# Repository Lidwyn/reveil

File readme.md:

# Alarm Clock Project

A fully custom-built **embedded alarm clock** designed from scratch, featuring a hardware-level implementation using an **ATmega328P**, **7-segment displays**, a **real-time clock (RTC)** module, and a modular audio system with microSD song storage.
This project integrates **embedded firmware**, **electronics design**, **PCB layout**, **CAD**, and **technical documentation**.

> This project is **still in progress**, every features or documents mentionned here might **not be complete or avaible yet**.

## Features
+ **Times display**
+ **Next alarm** on secondary display
+ Up to **15 one time (unique) and 15 weekly (non unique) independent alarms**
+ **Night Mode** - complete display blackout
+ **RTC-based accurate timekeeping** (with battery backup)

## Tech Stack & Tools

### Firmware
+ **Atmega328P** (bare-metal Arduino-style development)
+ **Arduino language** via **PlatformIO**
+ Interrupt-drivern logic
+ Low-power modes

### Elecrtonics & PCB
+ **Kicad** for schematic capture and PCB layout
+ Multi-voltage power stage (5V and 3.3V)

### Mechanical Design
+ **CATIA** for enclosure & mechanical parts

### Documentation
+ **LaTeX** for the user and technical manuals

## Project Architure
```
/Prog/          -> PlatformIO project for MCU firmware
/Schematic/     -> KiCad schematics & PCB files
/cad/           -> CATIA models for enclosure
/Latex/         -> Latex (and pdf) manual
```

## How It Works
1. The **ATmega328P** handles alarm logic, display control, and power management.
2. A **DS3231 RTC** maintains accurate time with battery backup. Through **I2C bus**.
3. On the same chips as the DS3231, we have an **AT24C32 EEPROM** that store the multiples alarms, the volume, and the brightness setup. Also with battery backup and through the same **I2C bus**.
4. Two four **7-segment display** and **9 leds**, driven by two **MAX7219** are in charge of the display. Through **SPI bus**.
5. A **DFPlayer** handle the audio, stored on a **microSD card**, with an integrated amplifier and an external speaker. Through a **Serial Port bus**.
5. 6 buttons for setup.

Find more information about the GUI on the manual:
- [Manuel fr](Latex/Manuel.pdf)

## Learning Objectives & Personal Development
This project in an opportunity to build **foundational embedded-systems skills** from scratch, inculding:
+ **Embedded C++ developpement** on microcontrollers
+ Designing and debugging **digital and mixed-signal electronics**
+ Understanting **RTCs**, **SD interfaces**, **multiplexing**, and **interrupt-driven systems**
+ **PCB worklow** from schematic to layout to fabrication
+ **Mechanical design** for electronics
+ Writing **clear and precise technical documentation** in **LaTeX**

## What I'm Most Proud Of
+ Implementing **deep sleep and interrupt-driven wake-up**, dramatically
reducing power consumption
+ Designing a **clean dual-voltage system** that support both 5V and 3.3V as the ATmega328P consumme less current at 3.3V further improving power consumption
+ Using **logical Mosfet** to cut unactive chips such as the audio chips, reducing noise to zero and reducing consumption
+ **Creating the entire device end-to-end** : firmware, electonics, PCB, mechanical parts, and documentation
+ Gaining practical **embedded engineering experience** from low to no prior knowledge

## How to Build / Run
### Hardware
1. Burn bootloader on the ATmega328P
2. Flash your microSD on FAT32
3. Insert microSD with you preferred alarm audio file with this typo `0001WhateverName.mp3`

### Firmware
1. Install **PlatformIO** (VS Codium extension)
2. Plug the alarm clock
3. Plug your computer into the USB C to seral adapter of the card
4. Adjust `upload_port = COM15` to your specific usb port in `/Prog/platformio.ini`
5. Upload firmware with `pio run --target upload`

## Status
This project is **still in development** :
+ Firmware : **working**, new features should be added and bugs fixed
+ PCB : **schematic is done**, PCB layout is not
+ Mechanical part : not started
+ Documenation : just the base of the french user manual version

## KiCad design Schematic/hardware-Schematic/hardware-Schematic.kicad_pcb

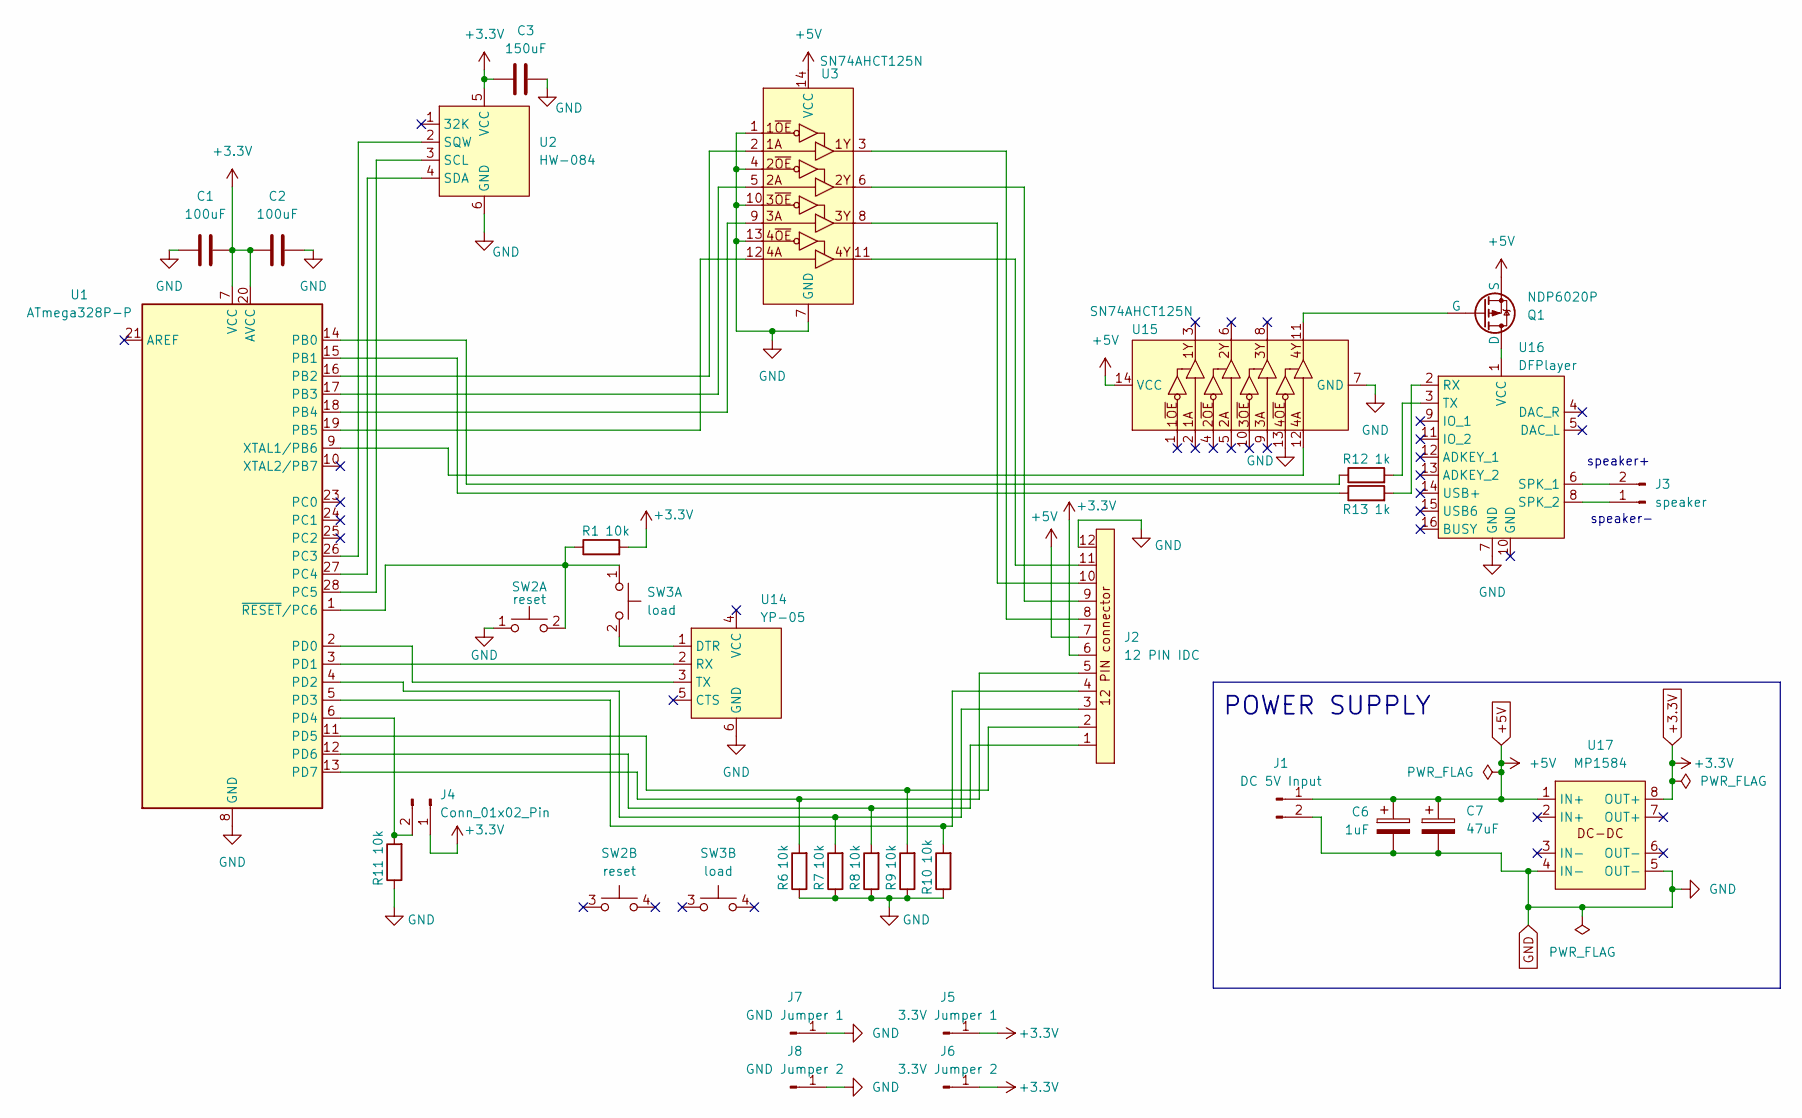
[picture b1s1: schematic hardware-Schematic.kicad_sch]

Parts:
C1, C2: 100uF; C_Axial_L12.0mm_D6.5mm_P15.00mm_Horizontal
C3: 150uF; C_Rect_L7.2mm_W3.0mm_P5.00mm_FKS2_FKP2_MKS2_MKP2
C6: 1uF; CP_Radial_D5.0mm_P2.50mm
C7: 47uF; CP_Radial_D5.0mm_P2.50mm
J1: DC 5V Input; USB-C DC input 5V
J2: 12 PIN IDC; IDC-Header_2x06_P2.54mm_Vertical
J3: speaker; TopButton
J4: Conn_01x02_Pin; R_Axial_DIN0207_L6.3mm_D2.5mm_P10.16mm_Horizontal
J5: 3.3V Jumper 1; Pin_D0.7mm_L6.5mm_W1.8mm_FlatFork
J6: 3.3V Jumper 2; Pin_D0.7mm_L6.5mm_W1.8mm_FlatFork
J7: GND Jumper 1; Pin_D0.7mm_L6.5mm_W1.8mm_FlatFork
J8: GND Jumper 2; Pin_D0.7mm_L6.5mm_W1.8mm_FlatFork
Q1: NDP6020P; TO-220F-3_Vertical
R1, R6, R7, R8, R9, R10, R11: 10k; R_Axial_DIN0207_L6.3mm_D2.5mm_P10.16mm_Horizontal
R12, R13: 1k; R_Axial_DIN0207_L6.3mm_D2.5mm_P10.16mm_Horizontal
SW2: reset; SW_PUSH_6mm
SW3: load; SW_PUSH_6mm
U1: ATmega328P-P; DIP-28_W7.62mm
U2: HW-084; HW-084_YP-05
U3, U15: SN74AHCT125N; DIP-14_W7.62mm
U14: YP-05; HW-084_YP-05
U16: DFPlayer
U17: MP1584

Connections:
+3.3V: C1.2, C2.1, C3.1, J2.6, J4.1, J5.1, J6.1, R1.2, U1.7 (VCC), U1.20 (AVCC), U2.5 (VCC), U17.8 (OUT+)
+5V: C6.1, C7.1, J1.1, J2.7, Q1.3 (S), U3.14 (VCC), U15.14 (VCC), U17.1 (IN+)
GND: C1.1, C2.2, C3.2, C6.2, C7.2, J1.2, J2.12, J7.1, J8.1, R6.1, R7.1, R8.1, R9.1, R10.1, R11.1, SW2.1 (C), U1.8 (GND), U1.22 (GND), U2.6 (GND), U3.1, U3.4, U3.7 (GND), U3.10, U3.13, U14.6 (GND), U15.7 (GND), U15.13, U16.7 (GND), U17.4 (IN-), U17.5 (OUT-)
unnamed: J2.8, U3.3
unnamed: J2.9, U3.6
unnamed: J2.10, U3.8
unnamed: J2.11, U3.11
unnamed: J3.1, U16.8 (SPK_2)
unnamed: J3.2, U16.6 (SPK_1)
unnamed: J4.2, R11.2, U1.6 (PD4)
unnamed: Q1.1 (D), U16.1 (VCC)
unnamed: Q1.2 (G), U15.11
unnamed: R1.1, SW2.2 (D), SW3.1 (C), U1.1 (~RESET/PC6)
unnamed: SW3.2 (D), U14.1 (DTR)
unnamed: R12.1, U1.14 (PB0)
unnamed: R13.1, U1.15 (PB1)
unnamed: U1.16 (PB2), U3.2
unnamed: U1.17 (PB3), U3.5
unnamed: U1.18 (PB4), U3.9
unnamed: U1.19 (PB5), U3.12
unnamed: U1.26 (PC3), U2.2 (SQW)
unnamed: U1.27 (PC4), U2.4 (SDA)
unnamed: U1.28 (PC5), U2.3 (SCL)
unnamed: U1.2 (PD0), U14.3 (TX)
unnamed: U1.3 (PD1), U14.2 (RX)
unnamed: J2.3, R7.2, U1.4 (PD2)
unnamed: J2.4, R10.2, U1.5 (PD3)
unnamed: J2.2, R9.2, U1.11 (PD5)
unnamed: J2.1, R8.2, U1.12 (PD6)
unnamed: J2.5, R6.2, U1.13 (PD7)
unnamed: U1.9 (XTAL1/PB6), U15.12
unnamed: R13.2, U16.2 (RX)
unnamed: R12.2, U16.3 (TX)

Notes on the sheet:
POWER SUPPLY
speaker+
speaker-

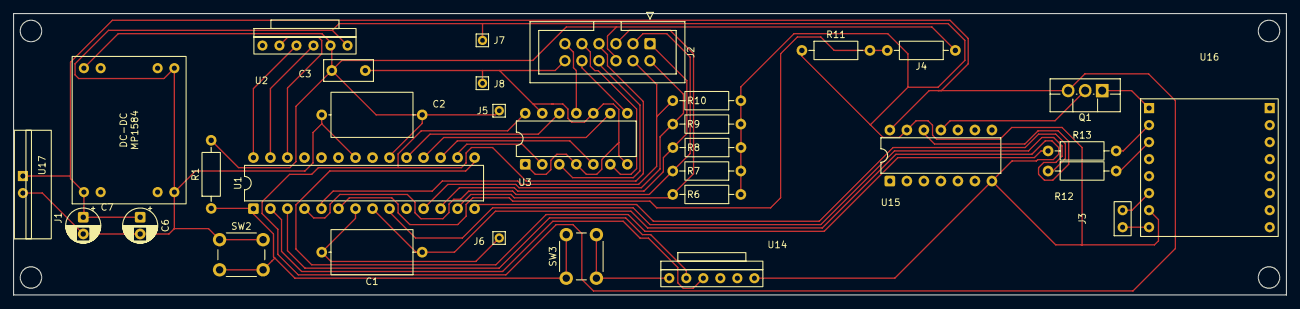
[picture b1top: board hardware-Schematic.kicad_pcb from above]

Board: 2 copper layers, 190.0 x 42.0 mm, 32 parts (0 on the bottom side), 33 nets.

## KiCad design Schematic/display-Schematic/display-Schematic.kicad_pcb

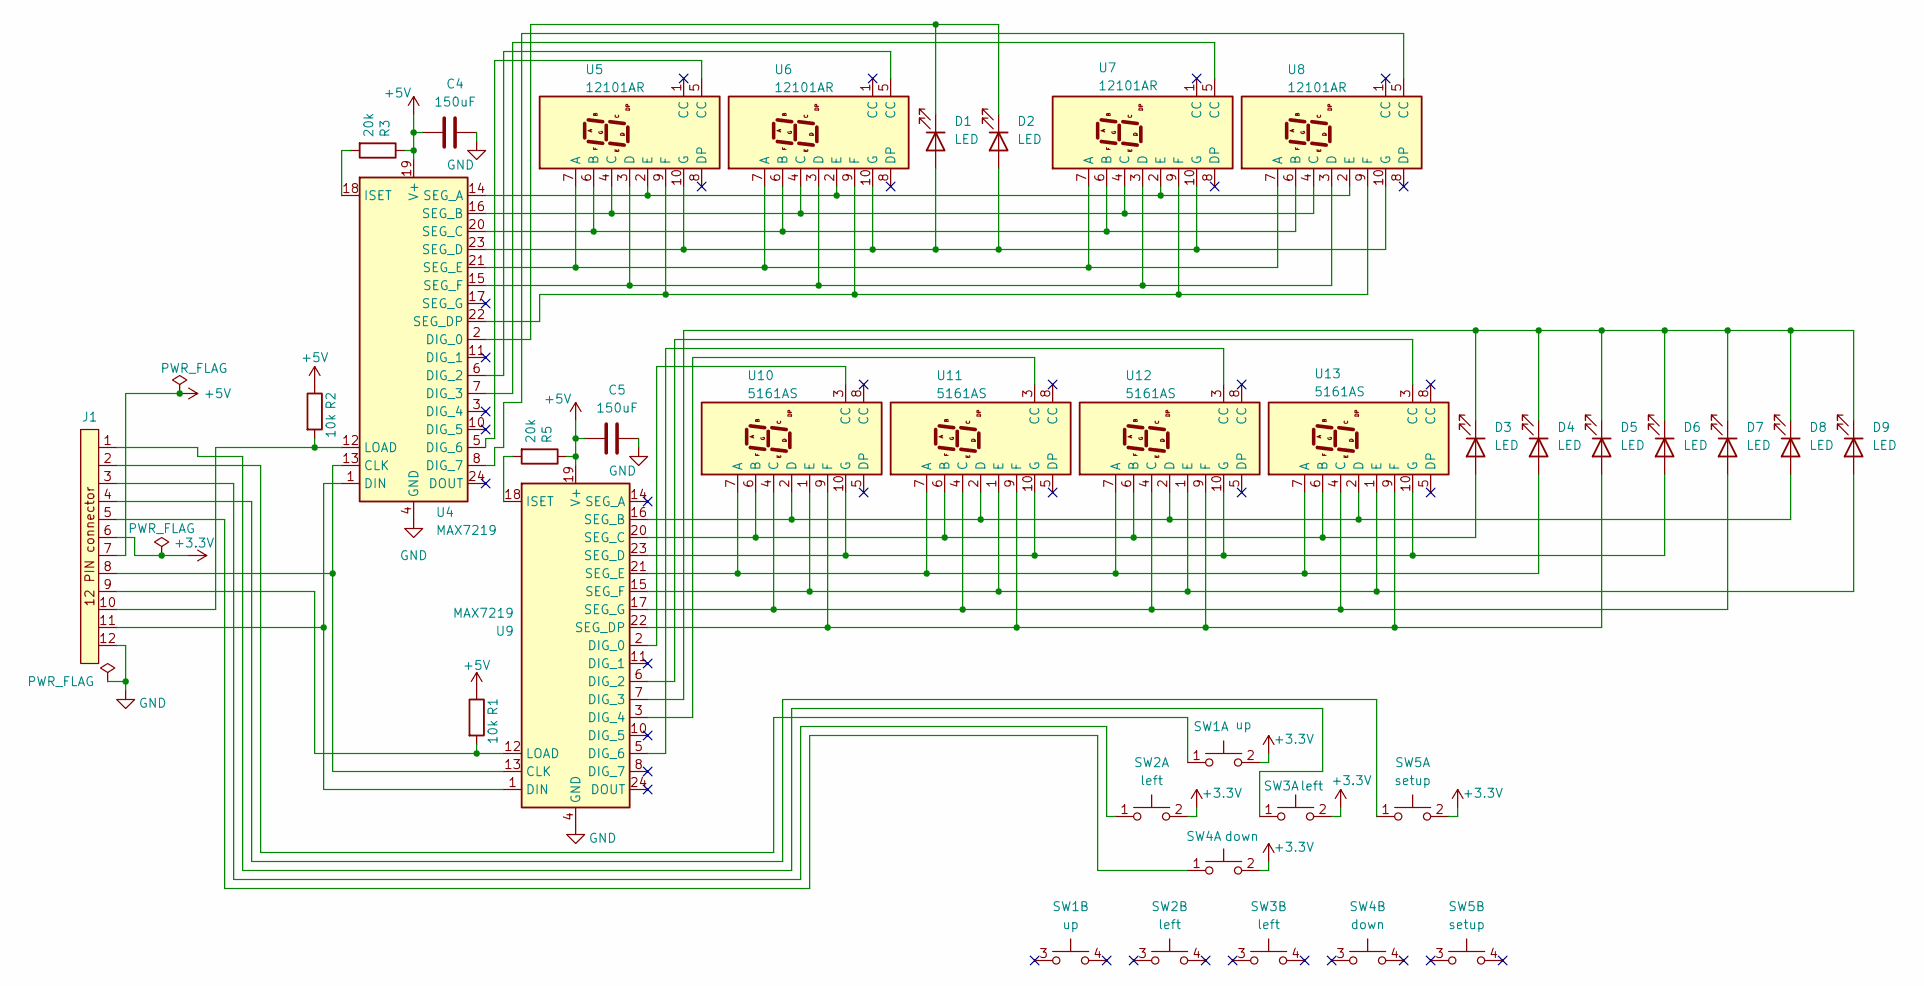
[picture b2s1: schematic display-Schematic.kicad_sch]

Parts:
C4, C5: 150uF; C_Rect_L7.2mm_W3.0mm_P5.00mm_FKS2_FKP2_MKS2_MKP2
D1, D2, D3, D4, D5, D6, D7, D8, D9: LED; LED_D5.0mm
J1: IDC-Header_2x06_P2.54mm_Vertical
R1, R2: 10k; R_Axial_DIN0207_L6.3mm_D2.5mm_P10.16mm_Horizontal
R3, R5: 20k; R_Axial_DIN0207_L6.3mm_D2.5mm_P10.16mm_Horizontal
SW1: up; SW_PUSH_6mm
SW2, SW3: left; SW_PUSH_6mm
SW4: down; SW_PUSH_6mm
SW5: setup; SW_PUSH_6mm
U4, U9: MAX7219; DIP-24_W7.62mm
U5, U6, U7, U8: 12101AR
U10, U11, U12, U13: 5161AS

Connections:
+3.3V: J1.6, SW1.2 (D), SW2.2 (D), SW3.2 (D), SW4.2 (D), SW5.2 (D)
+5V: C4.1, C5.1, J1.7, R1.1, R2.1, R3.1, R5.1, U4.19 (V+), U9.19 (V+)
GND: C4.2, C5.2, J1.12, U4.4 (GND), U4.9 (GND), U9.4 (GND), U9.9 (GND)
unnamed: D1.2 (A), D2.2 (A), U4.23 (SEG_D), U5.10 (G), U6.10 (G), U7.10 (G), U8.10 (G)
unnamed: D1.1 (K), D2.1 (K), U4.2 (DIG_0)
unnamed: D3.2 (A), U9.20 (SEG_C), U10.6 (B), U11.6 (B), U12.6 (B), U13.6 (B)
unnamed: D3.1 (K), D4.1 (K), D5.1 (K), D6.1 (K), D7.1 (K), D8.1 (K), D9.1 (K), U9.7 (DIG_3)
unnamed: D4.2 (A), U9.21 (SEG_E), U10.7 (A), U11.7 (A), U12.7 (A), U13.7 (A)
unnamed: D5.2 (A), U9.22 (SEG_DP), U10.9 (F), U11.9 (F), U12.9 (F), U13.9 (F)
unnamed: D6.2 (A), U9.23 (SEG_D), U10.10 (G), U11.10 (G), U12.10 (G), U13.10 (G)
unnamed: D7.2 (A), U9.17 (SEG_G), U10.4 (C), U11.4 (C), U12.4 (C), U13.4 (C)
unnamed: D8.2 (A), U9.16 (SEG_B), U10.2 (D), U11.2 (D), U12.2 (D), U13.2 (D)
unnamed: D9.2 (A), U9.15 (SEG_F), U10.1 (E), U11.1 (E), U12.1 (E), U13.1 (E)
unnamed: J1.2, SW1.1 (C)
unnamed: J1.3, SW2.1 (C)
unnamed: J1.1, SW3.1 (C)
unnamed: J1.5, SW4.1 (C)
unnamed: J1.4, SW5.1 (C)
unnamed: J1.8, U4.13 (CLK), U9.13 (CLK)
unnamed: U4.6 (DIG_2), U6.5 (CC)
unnamed: U4.7 (DIG_3), U7.5 (CC)
unnamed: U4.5 (DIG_6), U5.5 (CC)
unnamed: U4.8 (DIG_7), U8.5 (CC)
unnamed: J1.11, U4.1 (DIN), U9.1 (DIN)
unnamed: R3.2, U4.18 (ISET)
unnamed: J1.10, R2.2, U4.12 (LOAD)
unnamed: U4.14 (SEG_A), U5.2 (E), U6.2 (E), U7.2 (E), U8.2 (E)
unnamed: U4.16 (SEG_B), U5.4 (C), U6.4 (C), U7.4 (C), U8.4 (C)
unnamed: U4.20 (SEG_C), U5.6 (B), U6.6 (B), U7.6 (B), U8.6 (B)
unnamed: U4.22 (SEG_DP), U5.9 (F), U6.9 (F), U7.9 (F), U8.9 (F)
unnamed: U4.21 (SEG_E), U5.7 (A), U6.7 (A), U7.7 (A), U8.7 (A)
unnamed: U4.15 (SEG_F), U5.3 (D), U6.3 (D), U7.3 (D), U8.3 (D)
unnamed: U9.2 (DIG_0), U10.3 (CC)
unnamed: U9.6 (DIG_2), U13.3 (CC)
unnamed: U9.3 (DIG_4), U11.3 (CC)
unnamed: U9.5 (DIG_6), U12.3 (CC)
unnamed: R5.2, U9.18 (ISET)
unnamed: J1.9, R1.2, U9.12 (LOAD)

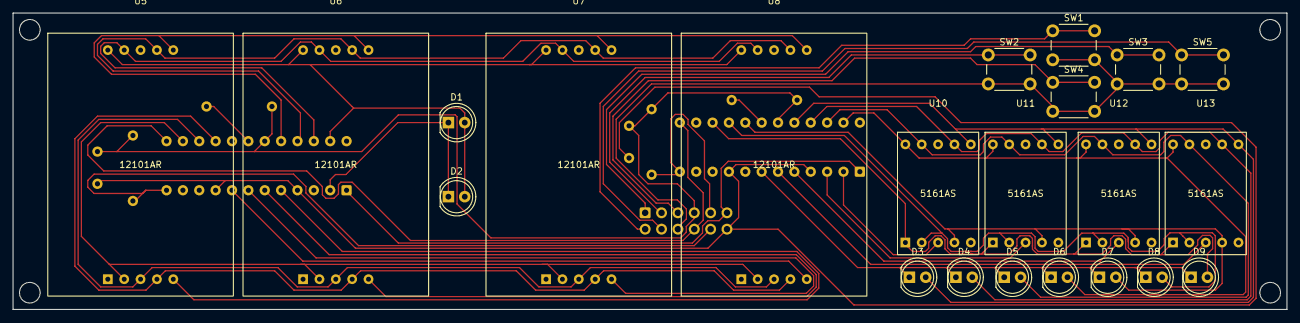
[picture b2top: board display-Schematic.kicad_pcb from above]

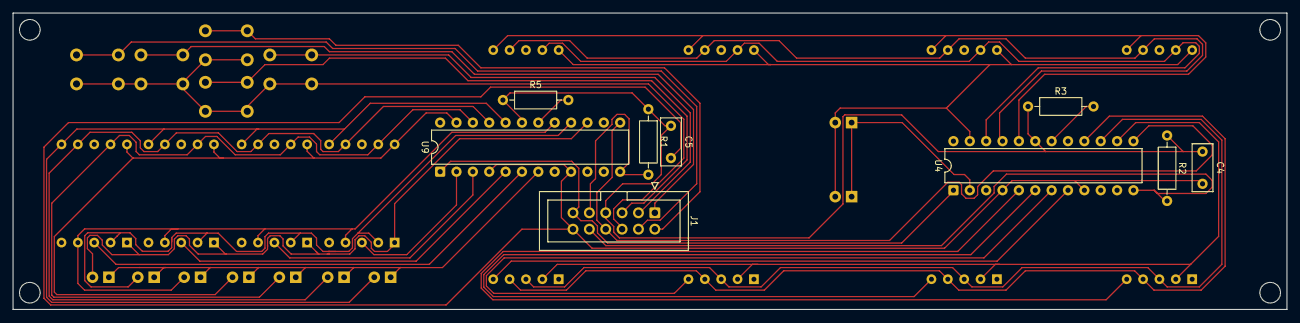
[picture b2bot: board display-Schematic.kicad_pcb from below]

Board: 2 copper layers, 197.7 x 46.0 mm, 31 parts (9 on the bottom side), 38 nets.

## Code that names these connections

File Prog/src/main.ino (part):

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//Audio
const uint8_t DFPrx = 8; // to TX
const uint8_t DFPtx = 9; // to RX
// const uint8_t DFPpower = A0; // Not A0 but PB6 which doesn't have number in the standard Arduino core
AltSoftSerial DFPlayerPort; // RX = D8/PB0 TX = D9/PB1 (forced)
bool isAwake = false;
bool isReset = false;
unsigned long alarmWakeUpTimer = 0; // This timer is for the delay between the DFPlayer turning on and the first UART transmission
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  AT24C32::begin(AT24C32addr, true, &Serial);

  //Interruption clock (1hz so two interruption per second -> passage 0-1 et 1-0)
  pinMode(A3, INPUT);         // DS3131 clock input on A3 (PC3)
  PCICR |= (1 << PCIE1);      // Activing interruptions on PCINT[14:8] --> PC0 to PC5 / A0 to A5
  PCMSK1 |= (1 << PCINT11);   // Activing interruption specifically on PCINT11 --> PC3 / A3
  
  //Interruption boutons
  PCICR |= (1 << PCIE2);      // Activing interruptions on PCINT[16:23] --> PD0 to PD7 / D0 to D7

  pinMode(btPlus, INPUT);     // pinMode button
  PCMSK2 |= (1 << PCINT21);   // Activing interruption
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
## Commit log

2025-09-27 sorting
2025-09-27 adding .gitignore
2025-09-28 debug menu setup fini, menu setup fonctionnel
2025-09-28 added hysteresis cycle for some switches, untested
2025-09-28 alarm selecting menu now accessible but unable to quit it, alarm setup still not debuged yet
2025-09-29 Switched to full VScodium with PlatformIO and clangd. Now require Minicore to be installed in /Prog/Minicore
2025-09-29 Alarm menu almost fully done, delete option to do, next step is debuging the alarm setup menu
2025-09-30 debug the main component of the alarm menu, alarm setup menu fully working, left to do : creating new alarm and handling no alarm (active and/or at all)
2025-10-01 debuged an issue with the calculation of the number of alarm existing in the storage, the reg data was shifted for no reason
2025-10-01 Added a little optimisation for the detection of both U and NU alarms
2025-10-01 Major issue fixed where modifyU and modifyNU would sometimes save modification and sometimes not with a very weird behaviour. Now works properly.
2025-11-20 small change for the alarm select menu going out of bound + now setting selectedAlarm to 1 (first in the list or create a new one if empty) when switching from unique to non-unique and vice versa
2025-11-20 corrected an issue with the findNextActiveAlarm function not finding the next alarm sometimes with NU alarms, now it works fine
2025-11-26 menuReveilDebug finished
2025-11-26 Untested, it's just a sketch with the audio part added
2025-11-27 Audio fully functionnal, ready for merge
2025-11-28 added a KiCad project in ./Schematic/
2025-11-28 added more content to the Latex file
2025-11-28 adding a readme
2025-11-28 Adding most of the content to readme.md
2025-12-08 corrected a but in modifyIsSetting and modifyAlarmIsSetting, it should correct a bug with setup value goind out of bound
2025-12-10 There will two PCB, one with the display and the buttons (execpt top button), and another with the hardware part. I keep the full schematic in full-schematic and I added two new project kickad projec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
2025-12-10 adjusted .gitignore, and corrected the 12 PIN IDC custom component's schematic
2025-12-10 started working on the PCB side of the display part
2025-12-12 Making the hardware schematic ready for PCB implementation
2025-12-12 USC-C to 5V DC plug added to custom lib
2025-12-19 created pcb part for hardware size, all object, but still need layout and connections
2025-12-19 started the rooting but some thing moved and now every thing is miss placed I must start from the beginning again
2025-12-23 Finished the display PCB. A lot of changes went throough to ensure only one layer was used for connections. To change : plug pin placement ; switches are now pull up ; in the code : digit codes are n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
2026-01-04 Further work on the hardware side of the pcb
2026-01-05 Finished the PCBs. I had to use two jumper cable. I also adjusted the position of some traces close to pins
2026-01-05 Created gerber files
2026-02-12 fixed the code for the actual pcb prototype
2026-02-14 corrected the issue with PB6 not being a natively supported port on arduino by righting directly in the registrers
2026-02-15 updataded the french manual, all informations are on it but layout must be improved, and I like to add better pictures
2026-02-16 updated the french manual
2026-02-18 now uploading for a linux device : update platformio.ini for linux and windows in a new folder :platformioIniVersion
2026-03-02 Corrected the french manual
2026-03-24 I miss soldered a component on the pcb and when dessoldering, I scratched trace, which lead to a lot of testing. I also updated the DS3231 lib to always re-write the 0x0E registrer to activate the cl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
2026-03-24 Major bugfix, from the last update. Basically I messed up two line which lead to calling a function on a un-referenced pointer, it was still working when testing, probably because it was randomly (or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
2026-03-31 Fixed an issue with alarm detection not working when in nightmode. Now also turning night mode off after an alarm ring
2026-03-31 Fixed a weird bug, I believe the DFPlayer waking up is causing a lot of weird stuff, and it was generating an error when using the I2C bus at the same time. I moved the auto desable of unique alarm a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
2026-04-01 updatade the simpleFrame. I also though I had a bug but it was a date mismatch, so I just added commentary.
2026-04-01 adjusted the frame
2026-04-01 Corrected the simple frame and printing it
